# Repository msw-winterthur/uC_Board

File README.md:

# [uC_Board Wiki](https://github.com/msw-winterthur/uC_Board/wiki)

Du brauchst [Hilfe](https://github.com/msw-winterthur/uC_Board/wiki) oder weisst nicht [wo Anfangen](https://github.com/msw-winterthur/uC_Board/wiki)? Besuche unbedingt das [Wiki](https://github.com/msw-winterthur/uC_Board/wiki)!

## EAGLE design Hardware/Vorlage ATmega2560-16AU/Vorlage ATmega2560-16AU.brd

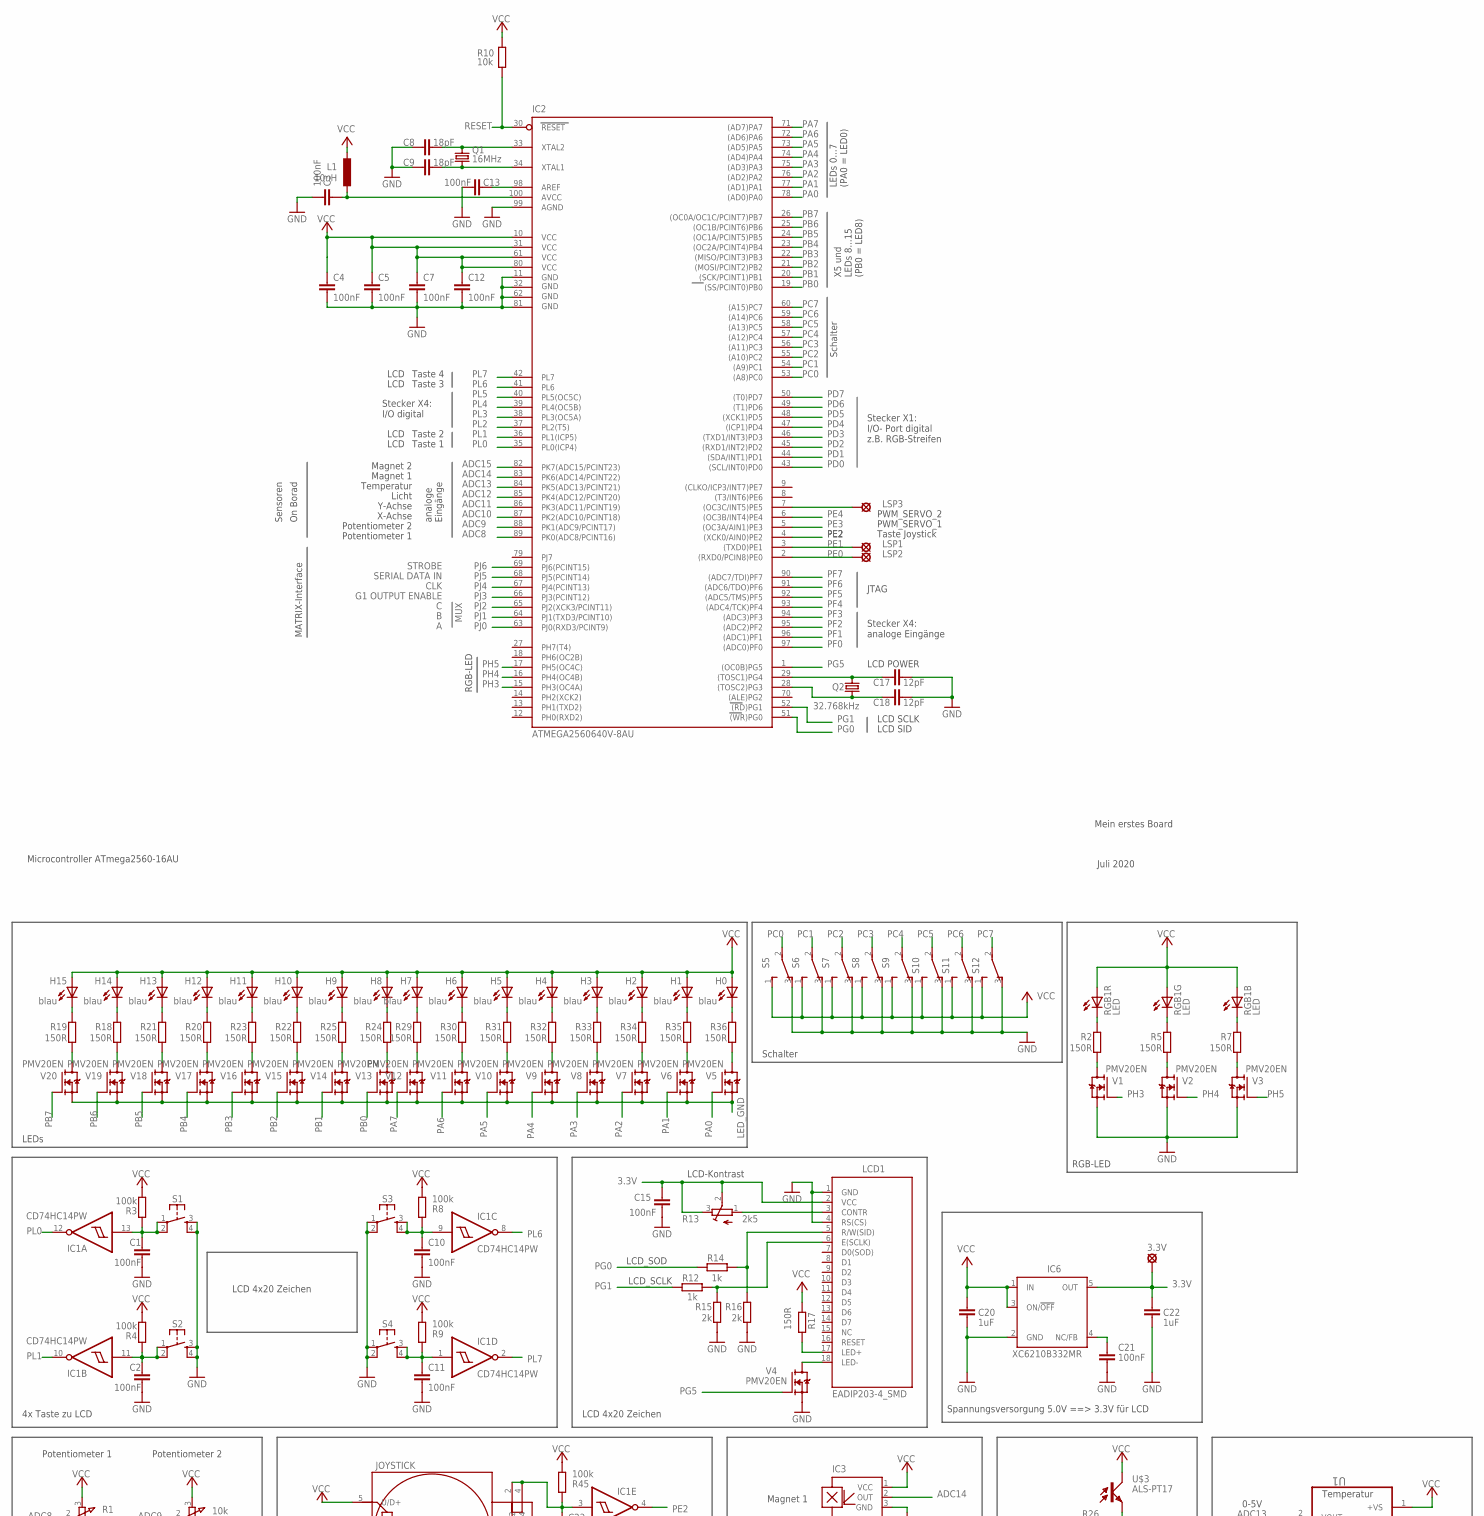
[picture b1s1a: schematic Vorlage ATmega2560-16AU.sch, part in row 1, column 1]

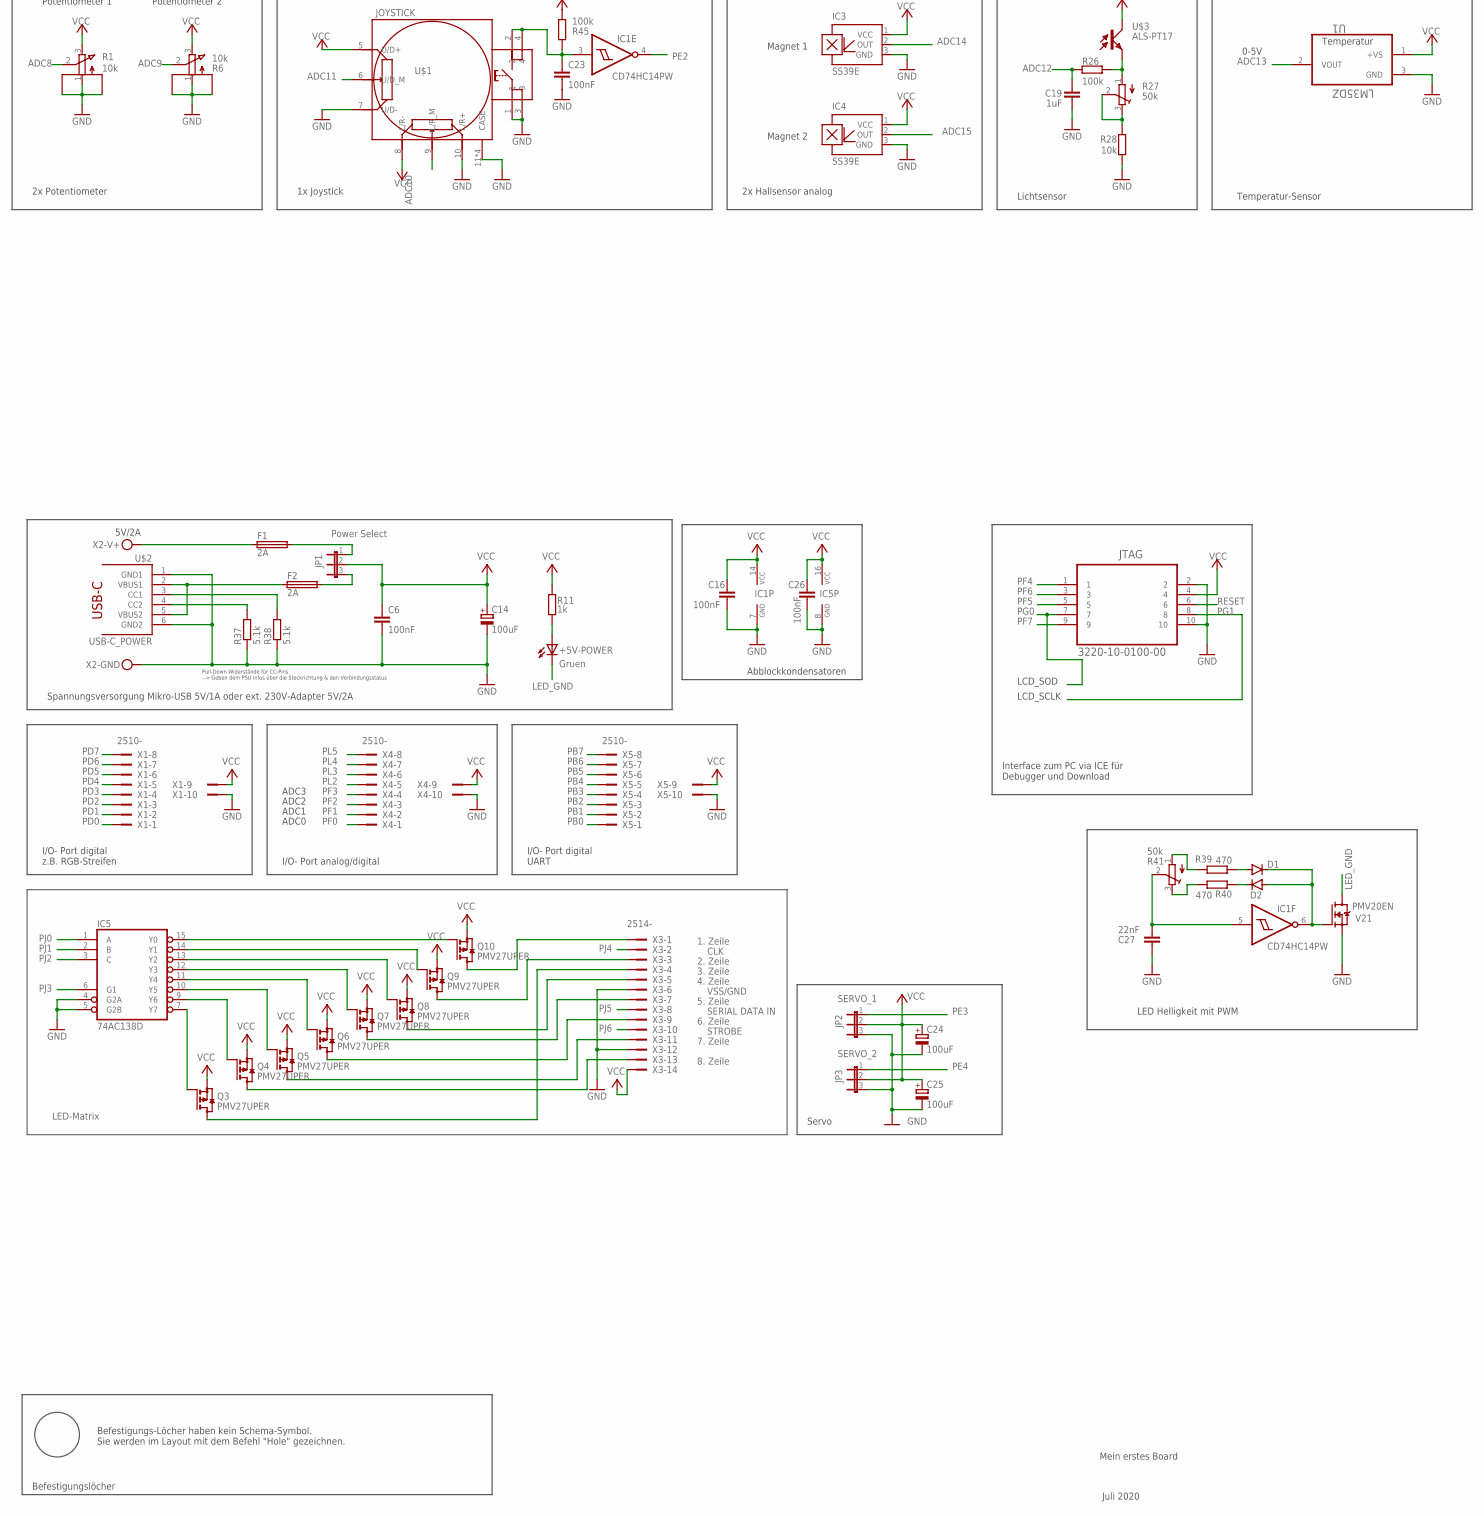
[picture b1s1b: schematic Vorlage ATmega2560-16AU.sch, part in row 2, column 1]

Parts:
3.3V: 3.3V; LSP11
+5V-POWER: Gruen; CHIPLED_1206
C1, C2, C3, C4, C5, C6, C7, C10, C11, C12, C13, C15, C16, C21, C23, C26: 100nF; C1206
C8, C9: 18pF; C0805K
C14, C24, C25: 100uF; UD-6,3X5,8_NICHICON
C17, C18: 12pF; C0805K
C19, C20, C22: 1uF; C1206
C27: 22nF; C0805
D1, D2: DIODE-SOD123; SOD123
F1, F2: 2A; F1206
H0, H1, H2, H3, H4, H5, H6, H7, H8, H9, H10, H11, H12, H13, H14, H15: blau; CHIPLED_1206
IC1: CD74HC14PW; SO14
IC2: ATMEGA2560640V-8AU; TQFP100
IC3, IC4: SS39E; SOT23-W
IC5: 74AC138D; SO16
IC6: XC6210B332MR; SOT23-DBV
JP1: Power Select; JP2
JP2: SERVO_1; JP2
JP3: SERVO_2; JP2
JTAG: 3220-10-0100-00; SAMTEC_FTS-105-01-L-D
L1: 10uH; L2825P
LCD1: EADIP203-4_SMD; EADIP203-4SMD
LSP1, LSP2, LSP3: LSP11
Q1: 16MHz; HC49UP
Q2: 32.768kHz; TC38H
Q3, Q4, Q5, Q6, Q7, Q8, Q9, Q10: PMV27UPER; SOT23
R1, R6: 10k; EVUF
R2, R5, R7, R17, R18, R19, R20, R21, R22, R23, R24, R25, R29, R30, R31, R32, R33, R34, R35, R36: 150R; R1206
R3, R4, R8, R9, R26, R45: 100k; R1206
R10, R28: 10k; R1206
R11, R12, R14: 1k; R1206
R13: 2k5; 3223G
R15, R16: 2k; R1206
R27, R41: 50k; 3223G
R37, R38: 5.1k; R0805
R39, R40: 470; R0805
RGB1: LED; LED_MIT_DIFUSOR
S1, S2, S3, S4: TS42_4PAD
S5, S6, S7, S8, S9, S10, S11, S12: TL36POSPDT_5MM; SPDT_5MM
U1: LM35DZ; TO127P254X495-3P
U$1: JOYSTICK; RKJXV1224005
U$2: USB-C_POWER; USB-C
U$3: ALS-PT17; SOD232-W
V1, V2, V3, V4, V5, V6, V7, V8, V9, V10, V11, V12, V13, V14, V15, V16, V17, V18, V19, V20, V21: PMV20EN; SOT23
X1, X4, X5: 2510-; PAK100/2500-10
X2: +5V; MKDSN1,5/2-5,08
X3: 2514-; PAK100/2500-14

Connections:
3.3V: 3.3V.MP, C15.1, C22.1, IC6.5 (OUT), LCD1.2 (VCC), R13.2 (S), R13.3 (E)
ADC8: IC2.89 (PK0(ADC8/PCINT16)), R1.2 (S)
ADC9: IC2.88 (PK1(ADC9/PCINT17)), R6.2 (S)
ADC10: IC2.87 (PK2(ADC10/PCINT18)), U$1.9 (L/R_M)
ADC11: IC2.86 (PK3(ADC11/PCINT19)), U$1.6 (U/D_M)
ADC12: C19.2, IC2.85 (PK4(ADC12/PCINT20)), R26.1
ADC13: IC2.84 (PK5(ADC13/PCINT21)), U1.2 (VOUT)
ADC14: IC2.83 (PK6(ADC14/PCINT22)), IC3.2 (OUT)
ADC15: IC2.82 (PK7(ADC15/PCINT23)), IC4.2 (OUT)
GND: C1.2, C2.2, C3.1, C4.2, C5.2, C6.2, C7.2, C8.1, C9.2, C10.2, C11.2, C12.2, C13.1, C14.-, C15.2, C16.2, C17.2, C18.2, C19.1, C20.2, C21.2, C22.2, C23.2, C24.-, C25.-, C26.2, C27.2, IC1.7 (GND), IC2.11 (GND), IC2.32 (GND1), IC2.62 (GND2), IC2.81 (GND3), IC2.99 (AGND), IC3.3 (GND), IC4.3 (GND), IC5.4 (G2A), IC5.5 (G2B), IC5.8 (GND), IC6.2 (GND), JP2.3, JP3.3, JTAG.2, JTAG.10, LCD1.1 (GND), LCD1.4 (RS(CS)), R1.1 (A), R1.M1, R1.M2, R6.1 (A), R6.M1, R6.M2, R15.1, R16.1, R28.1, R37.1, R38.1, S1.3, S1.4, S2.3, S2.4, S3.1, S3.2, S4.1, S4.2, S5.3 (O), S6.3 (O), S7.3 (O), S8.3 (O), S9.3 (O), S10.3 (O), S11.3 (O), S12.3 (O), U1.3 (GND), U$1.1, U$1.3, U$1.7 (U/D-), U$1.10 (L/R+), U$1.11 (CASE), U$1.12 (CASE), U$1.15 (CASE), U$1.16 (CASE), U$2.1 (GND1), U$2.6 (GND2), V1.2 (S), V2.2 (S), V3.2 (S), V4.2 (S), V21.2 (S), X1.10, X2.1.1, X2.1.2, X3.6, X3.12, X4.10, X5.10; also elsewhere on the board
H1: H15.C, R19.2
H7: H7.C, R29.2
LED_GND: +5V-POWER.C, V5.2 (S), V6.2 (S), V7.2 (S), V8.2 (S), V9.2 (S), V10.2 (S), V11.2 (S), V12.2 (S), V13.2 (S), V14.2 (S), V15.2 (S), V16.2 (S), V17.2 (S), V18.2 (S), V19.2 (S), V20.2 (S), V21.3 (D)
unnamed: R7.2, RGB1.1 (C)
unnamed: R5.2, RGB1.2 (C)
unnamed: F1.2, JP1.1
unnamed: F2.2, JP1.3
unnamed: R36.1, V5.3 (D)
unnamed: R35.1, V6.3 (D)
unnamed: R34.1, V7.3 (D)
unnamed: R38.2, U$2.3 (CC1)
unnamed: C23.1, IC1.3 (I), R45.1, U$1.2, U$1.4
unnamed: R37.2, U$2.4 (CC2)
unnamed: R2.2, RGB1.3 (C)
unnamed: LCD1.18 (LED-), V4.3 (D)
unnamed: R33.1, V8.3 (D)
unnamed: R32.1, V9.3 (D)
unnamed: R31.1, V10.3 (D)
unnamed: R30.1, V11.3 (D)
unnamed: R29.1, V12.3 (D)
unnamed: IC2.7 ((OC3C/INT5)PE5), LSP3.MP
unnamed: R26.2, R27.1 (A), U$3.E
unnamed: R27.2 (S), R27.3 (E), R28.2
unnamed: C1.1, IC1.13 (I), R3.2, S1.1, S1.2
unnamed: C2.1, IC1.11 (I), R4.2, S2.1, S2.2
unnamed: C11.1, IC1.1 (I), R9.1, S4.3, S4.4
unnamed: C10.1, IC1.9 (I), R8.1, S3.3, S3.4
unnamed: C9.1, IC2.34 (XTAL1), Q1.1
unnamed: C3.2, IC2.100 (AVCC), L1.2
unnamed: R2.1, V1.3 (D)
unnamed: R5.1, V2.3 (D)
unnamed: R7.1, V3.3 (D)
unnamed: C13.2, IC2.98 (AREF)
unnamed: F2.1, U$2.2 (VBUS1), U$2.5 (VBUS2)
unnamed: C17.1, IC2.29 ((TOSC1)PG4), Q2.1
unnamed: H6.C, R30.2
unnamed: LCD1.3 (CONTR), R13.1 (A)
unnamed: C18.1, IC2.28 ((TOSC2)PG3), Q2.2
unnamed: D1.C, D2.A, IC1.6 (O), V21.1 (G)
unnamed: C8.2, IC2.33 (XTAL2), Q1.2
unnamed: D1.A, R39.1
unnamed: LCD1.6 (E(SCLK)), R12.1, R15.2
unnamed: LCD1.5 (R/W(SID)), R14.1, R16.2
unnamed: D2.C, R40.1
unnamed: R39.2, R41.1 (A)
unnamed: R40.2, R41.3 (E)
unnamed: C27.1, IC1.5 (I), R41.2 (S)
unnamed: H14.C, R18.2
unnamed: H12.C, R20.2
unnamed: H2.C, R34.2
unnamed: H4.C, R32.2
unnamed: H5.C, R31.2
unnamed: H13.C, R21.2
unnamed: H10.C, R22.2
unnamed: H3.C, R33.2
unnamed: H11.C, R23.2
unnamed: H8.C, R24.2
unnamed: H0.C, R36.2
unnamed: H1.C, R35.2
unnamed: H9.C, R25.2
unnamed: +5V-POWER.A, R11.1
unnamed: R24.1, V13.3 (D)
unnamed: R25.1, V14.3 (D)
unnamed: R22.1, V15.3 (D)
unnamed: R23.1, V16.3 (D)
unnamed: R20.1, V17.3 (D)
unnamed: R21.1, V18.3 (D)
unnamed: R18.1, V19.3 (D)
unnamed: R19.1, V20.3 (D)
unnamed: C21.1, IC6.4 (NC/FB)
unnamed: F1.1, X2.2.1, X2.2.2
unnamed: LCD1.17 (LED+), R17.1
unnamed: IC5.15 (Y0), Q10.1 (G)
unnamed: Q10.3 (D), X3.1
unnamed: IC5.14 (Y1), Q9.1 (G)
unnamed: IC5.13 (Y2), Q8.1 (G)
unnamed: IC5.12 (Y3), Q7.1 (G)
unnamed: IC5.11 (Y4), Q6.1 (G)
unnamed: IC5.10 (Y5), Q5.1 (G)
unnamed: IC5.9 (Y6), Q4.1 (G)
unnamed: IC5.7 (Y7), Q3.1 (G)
unnamed: Q9.3 (D), X3.3
unnamed: Q3.3 (D), X3.4
unnamed: Q8.3 (D), X3.5
unnamed: Q7.3 (D), X3.7
unnamed: Q6.3 (D), X3.9
unnamed: Q5.3 (D), X3.11
unnamed: Q4.3 (D), X3.13
PA0: IC2.78 ((AD0)PA0), V5.1 (G)
PA1: IC2.77 ((AD1)PA1), V6.1 (G)
PA2: IC2.76 ((AD2)PA2), V7.1 (G)
PA3: IC2.75 ((AD3)PA3), V8.1 (G)
PA4: IC2.74 ((AD4)PA4), V9.1 (G)
PA5: IC2.73 ((AD5)PA5), V10.1 (G)
PA6: IC2.72 ((AD6)PA6), V11.1 (G)
PA7: IC2.71 ((AD7)PA7), V12.1 (G)
PB0: IC2.19 ((SS/PCINT0)PB0), V13.1 (G), X5.1
PB1: IC2.20 ((SCK/PCINT1)PB1), V14.1 (G), X5.2
PB2: IC2.21 ((MOSI/PCINT2)PB2), V15.1 (G), X5.3
PB3: IC2.22 ((MISO/PCINT3)PB3), V16.1 (G), X5.4
PB4: IC2.23 ((OC2A/PCINT4)PB4), V17.1 (G), X5.5
PB5: IC2.24 ((OC1A/PCINT5)PB5), V18.1 (G), X5.6
PB6: IC2.25 ((OC1B/PCINT6)PB6), V19.1 (G), X5.7
PB7: IC2.26 ((OC0A/OC1C/PCINT7)PB7), V20.1 (G), X5.8
PC0: IC2.53 ((A8)PC0), S5.2
PC1: IC2.54 ((A9)PC1), S6.2
PC2: IC2.55 ((A10)PC2), S7.2
PC3: IC2.56 ((A11)PC3), S8.2
PC4: IC2.57 ((A12)PC4), S9.2
PC5: IC2.58 ((A13)PC5), S10.2
PC6: IC2.59 ((A14)PC6), S11.2
PC7: IC2.60 ((A15)PC7), S12.2
PD0: IC2.43 ((SCL/INT0)PD0), X1.1
PD1: IC2.44 ((SDA/INT1)PD1), X1.2
PD2: IC2.45 ((RXD1/INT2)PD2), X1.3
PD3: IC2.46 ((TXD1/INT3)PD3), X1.4
PD4: IC2.47 ((ICP1)PD4), X1.5
PD5: IC2.48 ((XCK1)PD5), X1.6
PD6: IC2.49 ((T1)PD6), X1.7
PD7: IC2.50 ((T0)PD7), X1.8
PE0: IC2.2 ((RXD0/PCIN8)PE0), LSP2.MP
PE1: IC2.3 ((TXD0)PE1), LSP1.MP
PE2: IC1.4 (O), IC2.4 ((XCK0/AIN0)PE2)
PE3: IC2.5 ((OC3A/AIN1)PE3), JP2.1
PE4: IC2.6 ((OC3B/INT4)PE4), JP3.1
PF0: IC2.97 ((ADC0)PF0), X4.1
PF1: IC2.96 ((ADC1)PF1), X4.2
PF2: IC2.95 ((ADC2)PF2), X4.3
PF3: IC2.94 ((ADC3)PF3), X4.4
PF4: IC2.93 ((ADC4/TCK)PF4), JTAG.1
PF5: IC2.92 ((ADC5/TMS)PF5), JTAG.5
PF6: IC2.91 ((ADC6/TDO)PF6), JTAG.3
PF7: IC2.90 ((ADC7/TDI)PF7), JTAG.9
PG0: IC2.51 ((WR)PG0), JTAG.7, R14.2
PG1: IC2.52 ((RD)PG1), JTAG.8, R12.2
PG5: IC2.1 ((OC0B)PG5), V4.1 (G)
PH3: IC2.15 (PH3(OC4A)), V1.1 (G)
PH4: IC2.16 (PH4(OC4B)), V2.1 (G)
PH5: IC2.17 (PH5(OC4C)), V3.1 (G)
PJ0: IC2.63 (PJ0(RXD3/PCINT9)), IC5.1 (A)
PJ1: IC2.64 (PJ1(TXD3/PCINT10)), IC5.2 (B)
PJ2: IC2.65 (PJ2(XCK3/PCINT11)), IC5.3 (C)
PJ3: IC2.66 (PJ3(PCINT12)), IC5.6 (G1)
PJ4: IC2.67 (PJ4(PCINT13)), X3.2
PJ5: IC2.68 (PJ5(PCINT14)), X3.8
PJ6: IC2.69 (PJ6(PCINT15)), X3.10
PL0: IC1.12 (O), IC2.35 (PL0(ICP4))
PL1: IC1.10 (O), IC2.36 (PL1(ICP5))
PL2: IC2.37 (PL2(T5)), X4.5
PL3: IC2.38 (PL3(OC5A)), X4.6
PL4: IC2.39 (PL4(OC5B)), X4.7
PL5: IC2.40 (PL5(OC5C)), X4.8
PL6: IC1.8 (O), IC2.41 (PL6)
PL7: IC1.2 (O), IC2.42 (PL7)
RESET: IC2.30 (RESET), JTAG.6, R10.1; also elsewhere on the board
VCC: C4.1, C5.1, C6.1, C7.1, C12.1, C14.+, C16.1, C20.1, C24.+, C25.+, C26.1, H0.A, H1.A, H2.A, H3.A, H4.A, H5.A, H6.A, H7.A, H8.A, H9.A, H10.A, H11.A, H12.A, H13.A, H14.A, H15.A, IC1.14 (VCC), IC2.10 (VCC), IC2.31 (VCC1), IC2.61 (VCC2), IC2.80 (VCC3), IC3.1 (VCC), IC4.1 (VCC), IC5.16 (VCC), IC6.1 (IN), IC6.3 (ON/!OFF), JP1.2, JP2.2, JP3.2, JTAG.4, L1.1, Q3.2 (S), Q4.2 (S), Q5.2 (S), Q6.2 (S), Q7.2 (S), Q8.2 (S), Q9.2 (S), Q10.2 (S), R1.3 (E), R3.1, R4.1, R6.3 (E), R8.2, R9.2, R10.2, R11.2, R17.2, R45.2, RGB1.4 (A), RGB1.5 (A), RGB1.6 (A), S5.1 (S), S6.1 (S), S7.1 (S), S8.1 (S), S9.1 (S), S10.1 (S), S11.1 (S), S12.1 (S), U1.1 (+VS), U$1.5 (U/D+), U$1.8 (L/R-), U$3.C, X1.9, X3.14, X4.9, X5.9

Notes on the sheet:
Microcontroller ATmega2560-16AU
LCD SID
LCD SCLK
Taste 1
Taste 2
Taste 3
Taste 4
LCD
LCD POWER
Mein erstes Board
Juli 2020
JTAG
analoge Eingänge
G1 OUTPUT ENABLE
MUX
CLK
SERIAL DATA IN
STROBE
Magnet 2
Magnet 1
Temperatur
Licht
Y-Achse
X-Achse
Potentiometer 2
Potentiometer 1
Stecker X1: I/O- Port digital z.B. RGB-Streifen
MATRIX-Interface
Sensoren
On Borad
Stecker X4: analoge Eingänge
Stecker X4: I/O digital
Taste Joystick
PWM_SERVO_1
PWM_SERVO_2
I/O- Port digital UART
LCD 4x20 Zeichen
Spannungsversorgung Mikro-USB 5V/1A oder ext. 230V-Adapter 5V/2A
Spannungsversorgung 5.0V ==> 3.3V für LCD
Interface zum PC via ICE für Debugger und Download

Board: 2 copper layers, 160 parts (0 on the bottom side), 166 nets, no tracks yet.

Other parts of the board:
S13: TS42_4PAD

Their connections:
GND: S13.1, S13.2; also elsewhere on the board
RESET: S13.3, S13.4; also elsewhere on the board

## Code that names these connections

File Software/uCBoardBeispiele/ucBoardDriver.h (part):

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    ADC_05_NOT_USED,            //Nicht in Gebrauch
    ADC_06_NOT_USED,            //Nicht in Gebrauch
    ADC_07_NOT_USED,            //Nicht in Gebrauch
    ADC_08_POTI_1,              //Board: Potentiometer 1 (PK0, R1)
    ADC_09_POTI_2,              //Board: Potentiometer 2 (PK1, R6)
    ADC_10_JOYSTICK_X,          //Board: Joystick X (PK2)
    ADC_11_JOYSTICK_Y,          //Board: Joystick Y (PK3)
    ADC_12_LICHT,               //Board: Sichtsensor (PK4)
    ADC_13_TEMPERATUR,          //Board: Temperatursensor (PK5)
    ADC_14_MAGNET_1,            //Board: Magnetsensor 1 (PK6, IC3)
    ADC_15_MAGNET_2             //Board: Magnetsensor 2 (PK6, IC4)
    } adcChannel_t;

/**
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
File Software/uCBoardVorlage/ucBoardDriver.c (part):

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    //Eingang mit Pullups
    PORTE   = 0xFF;
    DDRE    = 0x00;
    //Taster Joystick (PE2) ohne PullUp
    PORTE   = PORTE & 0b11111011;
    //PORTF (ADC, X4) Eingang ohne PullUps
    PORTF   = 0x00;
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//****************************************************************** MATRIX-Treiber ******************************************************************//


#define ENABLE_0          PORTJ &= ~0x08; // PJ3 Zeilen/Mux ausschalten
#define ENABLE_1          PORTJ |=  0x08; // PJ3 Zeilen/Mux einschalten
#define CLOCK_0           PORTJ &= ~0x10; // PJ4 Clock = 0
#define CLOCK_1           PORTJ |=  0x10; // PJ4 Clock = 1
#define STROBE_0          PORTJ &= ~0x40; // PJ6 Strobe = 0
#define STROBE_1          PORTJ |=  0x40; // PJ6 Strobe = 1

#define DATA_Modul_1_ON   PORTJ |=  0x20; // PJ5 Data = 1
#define DATA_Modul_1_OFF  PORTJ &= ~0x20; // PJ5 Data = 0



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
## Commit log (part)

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2020-10-22 Fertiges uC-Board Layout
2020-10-22 Gerberfiles von Bestellung hinzugefügt
2020-10-22 Vorlage für Layouttage hinzugefügt
2020-10-22 Bestückungshinweise hinzugefügt
2020-10-22 BOM hinzugefügt
2020-10-22 Softwarevorlage und HW Test hinzugefügt
2020-10-22 Taster
    Taster neu auf PortL, Taster Joystick hinzugefügt
2020-10-22 Taster korrigiert
2020-10-23 SW Vorlage an board angepasst
2020-10-24 ICE-PCBA und JTag stecker hinzugefügt
2020-10-26 Neuer Treiber und Beispiele
2020-10-26 add systime to example, write zahl 64 bit now
2020-10-26 systime 1ms und writeZahl korrigiert
2020-10-26 Vorlage hinzugefügt
2020-10-26 warnings in beispiele entfernt
2020-10-26 warnings in driver entfern
2020-10-26 kommentar 5ms->1ms korrigiert
2020-10-27 Matrix treiber update
2020-10-27 treiber aufgeràumt IO-Funktionen hinzugefügt
2020-10-27 added io functions
2020-10-29 JTAG Stecker korrigiert
2020-10-29 rgb-Test mit buttons
2020-10-29 Potitest korrigiert
2020-10-30 Treiber aufgeräumt und kommentiert
2020-11-03 Unbenennen von pinInit und PinBsp hinzugefügt
2020-11-03 Hardware aufgeräumt
2020-11-03 Vorlagen angepasst
2020-11-03 Comments in vorlage formatiert
2020-11-04 Micro USB für JTAG hinzugefügt
2020-11-19 ledRead hinzugefügt
2021-02-09 Buttons Schalter und LEDs einzeln ansteuer- und lesbar
2021-02-09 Schalter Active High Low einstellbar
2021-02-09 removed wait for systemtick added waitforsystemtime instead
2021-04-08 Kompatibler Treiber für MoccaBoard hinzugefügt
2021-06-09 LEDs neu über FET
2021-06-09 Sicherung F1 ist 2A
2021-06-18 Update für version 2021 (EK20)
2021-06-25 print in uc vorlage
    muss noch in mocca bsp und vorlage und uc vorlage
2021-06-25 lcdLog mit formatted string
    fehlt noch in uc bsp und mocca bsp und vorlage
2021-06-25 formatted text in log und write
    fehlt in bsp und mocca
2021-06-25 uC-Board driver mit Log und formatted write
2021-06-25 formatted text in lcd write and added lcd log
2021-08-23 PortB an X5 geführt
    PortB ist nun mit LEDs und auf X5 geführt
2021-08-23 Uart auf X5 geführt
2021-08-23 Netzklasse Power ergänzt
2021-08-25 Checkliste hinzugefügt
2021-08-25 Lineal hinzugefügt
2021-08-25 Schema neu angeordnet
2021-08-25 DRC und ERC zu Checkliste hinzugefügt
2021-08-26 Layouthinweise hinzugefügt
2021-08-26 Sensoren ergänzt
2021-08-26 PortK ADC erwähnen...
2021-08-26 Korrektur ADC Erwähnung
2021-08-26 Name auf Checkliste
2021-08-30 neuer MSW-Header
2021-08-30 LEDs nicht mehr invertiert weil via FET
2021-09-02 Hardwarestruktur und Programmtestprotokoll hinzugefügt, Dokumente aufgeräumt
2021-09-09 Neuer Lichtsens und Jtag Buchse
2021-09-09 original fuses added
2021-09-10 Neuer Lichtsens gedreht....
2021-09-10 Stückzahlen und 50k Trimmer aktualisiert
2021-09-10 Bessere LED-Show
2021-09-17 Bestand in BOM aufgenommen
2021-09-23 neue RGB-LED
2021-09-23 schalterpositionen hinzugefügt
2021-09-24 LEDs leuchten beim Aufstarten nicht mehr auf
2021-09-24 Start Animation hinzugefügt
2021-10-04 log wait hinzugeffügt
2021-11-11 Anzahl Zeilen kann für lcdLog-Funktioenen eingestellt werden
2021-11-19 Switch active high kann in main gesetzt werden
2021-11-19 Revert "Switch active high kann in main gesetzt werden"
    This reverts commit 727724b0e186165211dfac5a4d8f45e1ea2201e4.
2022-01-14 Verweis auf Wiki
2022-01-14 Verlinkung Wiki
2022-03-11 Update wait for system time
2022-03-24 Netzteil (USB-C) hinzugefügt
2022-04-01 comment formated string
2022-05-11 added lcdShowText
2022-08-22 Herstellungsdokumente erstellt/angepasst
2022-08-24 Höhe Bottom hinzugefügt
2022-08-24 Quarz Q2 richtig verbunden
2022-08-25 Alle verwendeten Ports und ADCs hinzugefügt
2022-08-25 Bestand aktualisiert
2022-09-23 Added fuses screenshots doc
2022-12-02 Etiketten für Bauteillager hinzugefügt
2022-12-02 Bestand Materialliste aktualisiert
2023-03-15 Ports und uC entfernt
2023-03-15 Ports entfernt
2023-05-12 Keine InitShow mehr, Kommentar für Konstanten
2023-06-30 Reaktionszeit in Programmtestprotokoll
2023-06-30 Hardwarestruktur und Testprotokoll zusammengelegt.
2023-10-23 CC-Pins hinzugefügt (0805)
    Ich habe beim POWER Block zwei 5.1k Widerstände hinzugefügt. Mit denen sollte es definitiv kein problem sein 250mA zu ziehen.
2023-11-01 Tippfehler
2023-11-01 Globale interrupts in startsystime
2024-03-25 adcRead keine feste Wartezeit
    Ein Flag in ADC-Read wurde nicht richtig abgewartet, wodurch eine konstante Wartezeit verwendet werden musste. Dies ist korrigiert.
2024-07-19 Bestand aktualisiert von Raul und Ayana EK22
2024-07-22 LED Helligkeit mit einstellbarem PWM
2024-07-22 LED Helligkeit mit PWM
2024-07-22 5.1kR Widerstände in BOM und Kommentar in Schema gelöscht
2024-07-22 Reset button hinzugefügt
2024-08-17 Folder Rename
2024-08-17 Move Eagle-Files in Folder
2024-08-17 Add Fusion File
2024-08-17 LED-Helligkeitspoti und ResetButton hinzugefügt
2024-08-21 Netzklassen angepasst
2024-08-22 Checkliste ergänzt / Tipps und Tricks hinzugefügt
2025-02-27 add lcdCustomChar
2025-09-05 Etiketten ergänzt
2025-09-05 Bestand aktuallisiert
2025-09-05 Checkliste diverse Ergänzungen
